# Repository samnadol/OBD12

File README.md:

# OBD12

OBD-II dongle that bridges a vehicle's CAN bus (ISO 15765-4, 500 kbit/s) to Bluetooth LE and USB-C serial.

- `pcb/`: KiCad 9 schematic and layout
- `firmware/OBD12/`: STM32G431 firmware (STM32CubeIDE or PlatformIO)
- `firmware/BLUENRG-M2SP_DTM_SPI.hex`: image for the BLE module
- `software/`: Python host library and CLI
- `docs/protocol.md`: host protocol

## Hardware

- STM32G431KBT6, 32 MHz HSE
- TCAN337 CAN transceiver on FDCAN1. No termination fitted (R16/R17/C18 are DNP for bench use).
- BlueNRG-M2SP over SPI1
- FT230X USB UART on USART1, 115200 8N1
- Powered from OBD pin 16 (12 V vehicles only) or USB-C. LM2842 buck and SPX3819 LDO, OR'd with LM66100 ideal diodes, USB has priority.
- SWD on Tag-Connect TC2030-NL: J1 for the STM32, J5 for the BlueNRG. The board must be powered while programming.

LEDs: PWR (3.3 V), S1 (on idle, blinks with a BLE connection), S2 (CAN bus healthy and ECUs responding), RX/TX (USB).

## Setup

1. Flash `BLUENRG-M2SP_DTM_SPI.hex` to the BLE module through J5.
2. Flash the STM32 firmware through J1.
3. Program the FT230X EEPROM with FT_PROG so its serial number starts with `OBD12_`. The host library finds the board by this serial.

## Firmware

- **CubeIDE:** import `firmware/OBD12` as an existing project.
- **PlatformIO:** from `firmware/OBD12`, run `pio run`, or `pio run -t upload` to flash with an ST-Link. Keep its include paths in sync with `.cproject`.

The firmware is a main loop: interrupts only fill ring buffers or set flags, and a 3 s watchdog resets the MCU if the loop stalls. USB and BLE (Nordic UART service) carry the same framed protocol.

BLE pairing uses a passkey derived from the MCU UID; `info` over USB shows it. Over BLE, reset, clear bonds and non-read-only OBD requests (e.g. clearing DTCs) need a paired link.

## Software

```
cd software
pip install -r requirements.txt
python -m obd12 info          # USB, auto-detected
python -m obd12 --ble live    # BLE
```

Commands: `info`, `power`, `can-stats`, `vin`, `pids`, `obd`, `live`, `log`, `ping`, `reset`, `clear-bonds`.

The firmware reads the VIN and the vehicle's supported mode 01 PIDs at startup. `pids` lists them, and `live --pids supported` polls all of them (up to 32). The web app reads both when it connects and offers every supported PID in its live data section.

`software/web/` is a browser app using Web Bluetooth (Bluefy on iOS, Chrome or Edge elsewhere) or Web Serial for USB (desktop Chrome or Edge). It shows the vehicle's make and model (decoded from the VIN with [corgi](https://github.com/cardog-ai/corgi), which downloads a 25 MB copy of the NHTSA vPIC database the first time it sees a new VIN), live gauges with CSV recording, and trouble codes. Diagnostics such as power, CAN statistics and the device log stay in the CLI. It keeps one connection open and reconnects on its own. It has no build step, but it must be served over HTTPS or from `localhost`:

```
cd software/web
python3 -m http.server     # http://localhost:8000
```

Pushes to `master` that touch `software/web/` publish it to GitHub Pages (`.github/workflows/pages.yml`) at https://samnadol.github.io/OBD12/.

## Known issues

- No output capacitor directly on the USB LDO output (`USB_REG_OUT`).
- The power priority logic depends on LM66100 `ST` polarity. Check that 3.3 V stays up with USB and 12 V both connected.
- The ADC reads the regulator outputs without a divider, so the readings sit near full scale. They only work as presence detection.
- Check that C23 on the 12 V rail is rated for at least 25 V.
- R10/R11 (60 Ω) drive the FT230X LEDs harder than the CBUS default.
- When running on 12 V only, PA9 back-powers the unpowered FT230X.
- U9 pad 21 (GND) is unconnected in the netlist.
- No reverse-polarity protection on the 12 V input.

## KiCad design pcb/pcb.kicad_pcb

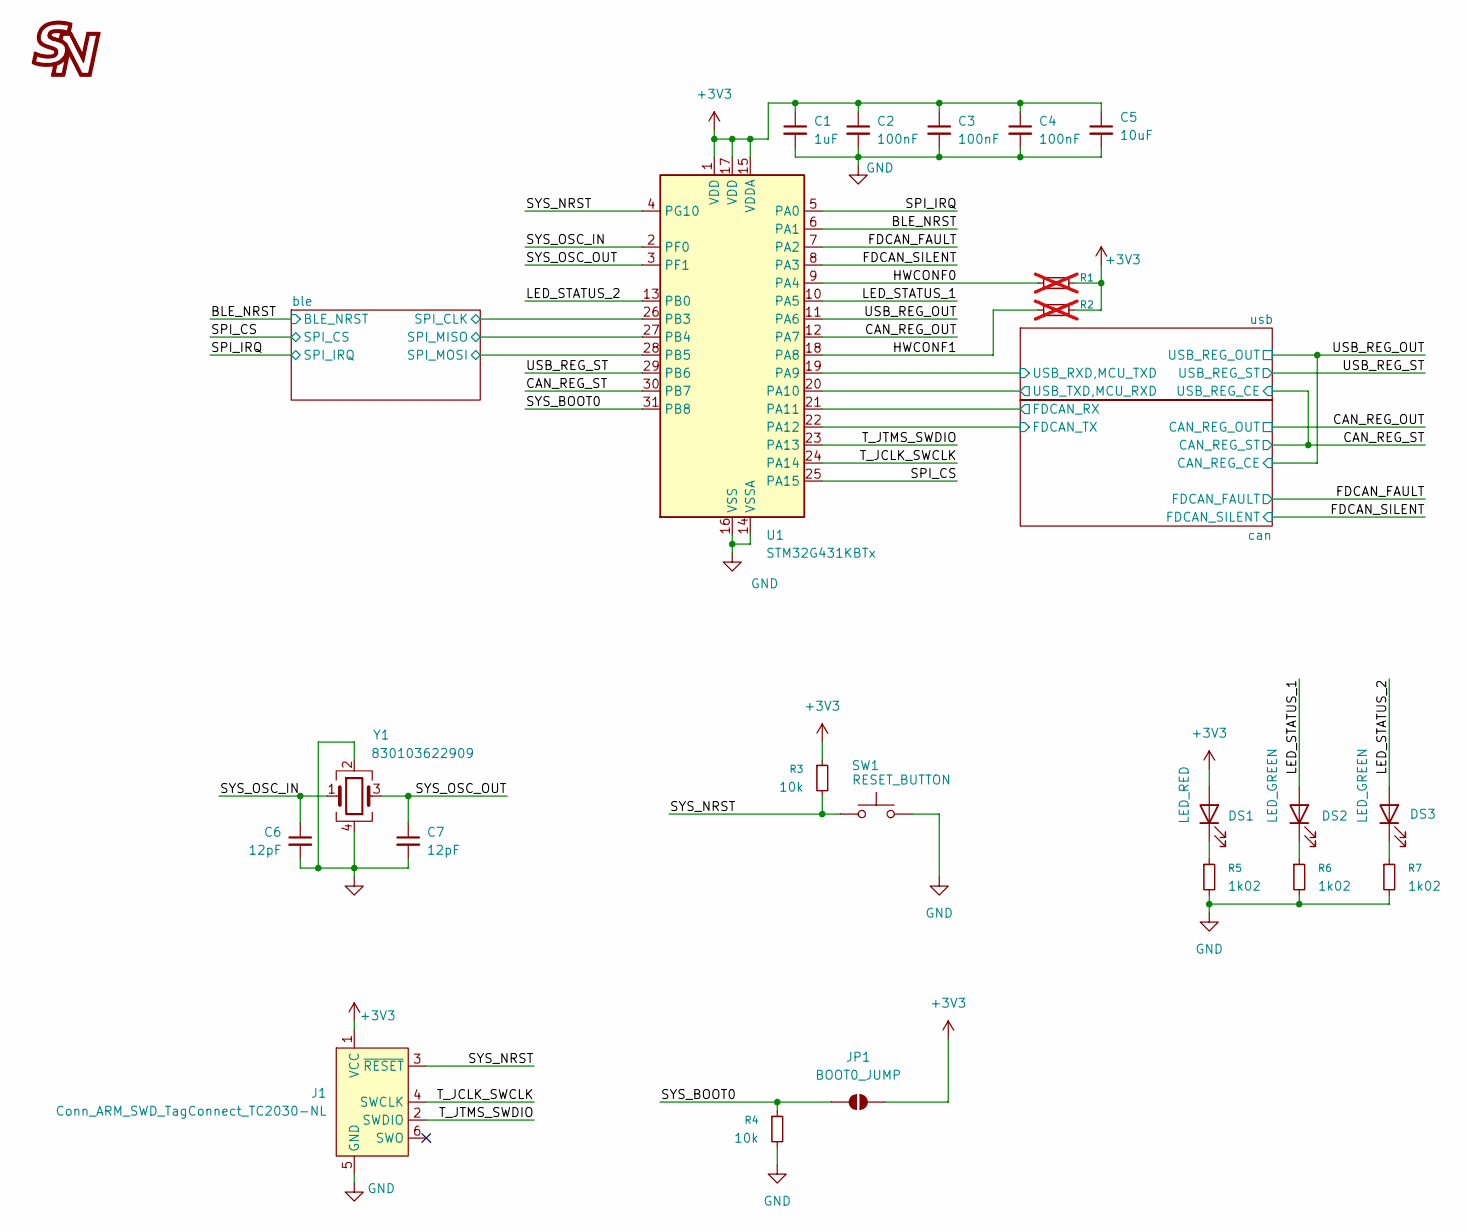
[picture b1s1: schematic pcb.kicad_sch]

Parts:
C1: 1uF; C_0603_1608Metric; LCSC C559769
C2, C3, C4: 100nF; C_0603_1608Metric; LCSC C14663
C5: 10uF; C_0603_1608Metric; LCSC C92487
C6, C7: 12pF; C_0603_1608Metric; LCSC C107034
DS1: LED_RED; LED_0603_1608Metric; LCSC C965799
DS2, DS3: LED_GREEN; LED_0603_1608Metric; LCSC C965804
G1: LOGO; logo
J1: Conn_ARM_SWD_TagConnect_TC2030-NL; Tag-Connect_TC2030-IDC-NL_2x03_P1.27mm_Vertical
JP1: BOOT0_JUMP; SolderJumper-2_P1.3mm_Open_Pad1.0x1.5mm
R1, R2: 0R; R_0603_1608Metric; LCSC C21189; not fitted
R3, R4: 10k; R_0603_1608Metric; LCSC C25804
R5, R6, R7: 1k02; R_0603_1608Metric; LCSC C22831
SW1: RESET_BUTTON; TS-1187A-ABAB; LCSC C318884
U1: STM32G431KBTx; LQFP-32_7x7mm_P0.8mm; LCSC C5270317
Y1: 830103622909; Crystal_SMD_3225-4Pin_3.2x2.5mm; LCSC C9009

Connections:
+3V3: C1.1, C2.1, C3.1, C4.1, C5.1, DS1.2 (A), J1.1 (VCC), JP1.2 (B), R1.2, R2.2, R3.1, U1.1 (VDD), U1.15 (VDDA), U1.17 (VDD); also elsewhere on the board
/BLE_NRST: U1.6 (PA1); also elsewhere on the board
/CAN_REG_OUT: U1.12 (PA7); also elsewhere on the board
/CAN_REG_ST: U1.30 (PB7); also elsewhere on the board
/FDCAN_FAULT: U1.7 (PA2); also elsewhere on the board
/FDCAN_SILENT: U1.8 (PA3); also elsewhere on the board
/HWCONF0: R1.1, U1.9 (PA4)
/HWCONF1: R2.1, U1.18 (PA8)
/LED_STATUS_1: DS2.2 (A), U1.10 (PA5)
/LED_STATUS_2: DS3.2 (A), U1.13 (PB0)
/SPI_CS: U1.25 (PA15); also elsewhere on the board
/SPI_IRQ: U1.5 (PA0); also elsewhere on the board
/SYS_BOOT0: JP1.1 (A), R4.1, U1.31 (PB8)
/SYS_NRST: J1.3 (~RESET), R3.2, SW1.1, U1.4 (PG10)
/SYS_OSC_IN: C6.1, U1.2 (PF0), Y1.1
/SYS_OSC_OUT: C7.1, U1.3 (PF1), Y1.3
/T_JCLK_SWCLK: J1.4 (SWCLK), U1.24 (PA14)
/T_JTMS_SWDIO: J1.2 (SWDIO), U1.23 (PA13)
/USB_REG_OUT: U1.11 (PA6); also elsewhere on the board
/USB_REG_ST: U1.29 (PB6); also elsewhere on the board
/ble/SPI_CLK: U1.26 (PB3); also elsewhere on the board
/ble/SPI_MISO: U1.27 (PB4); also elsewhere on the board
/ble/SPI_MOSI: U1.28 (PB5); also elsewhere on the board
/can/FDCAN_RX: U1.21 (PA11); also elsewhere on the board
/can/FDCAN_TX: U1.22 (PA12); also elsewhere on the board
/usb/USB_RXD,MCU_TXD: U1.19 (PA9); also elsewhere on the board
/usb/USB_TXD,MCU_RXD: U1.20 (PA10); also elsewhere on the board
GND: C1.2, C2.2, C3.2, C4.2, C5.2, C6.2, C7.2, J1.5 (GND), R4.2, R5.2, R6.2, R7.2, SW1.2, U1.14 (VSSA), U1.16 (VSS), U1.32 (VSS), Y1.2, Y1.4; also elsewhere on the board
unnamed: DS1.1 (K), R5.1
unnamed: DS2.1 (K), R6.1
unnamed: DS3.1 (K), R7.1

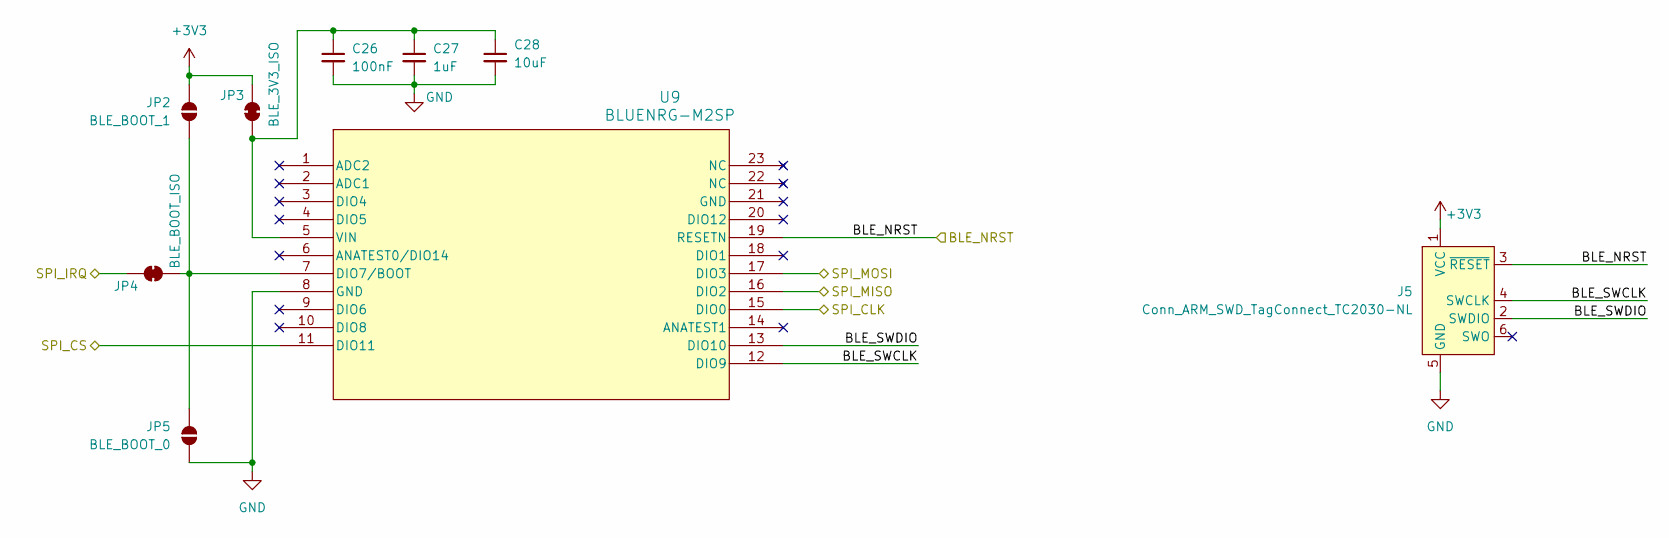
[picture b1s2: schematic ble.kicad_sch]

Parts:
C26: 100nF; C_0603_1608Metric; LCSC C14663
C27: 1uF; C_0603_1608Metric; LCSC C559769
C28: 10uF; C_0603_1608Metric; LCSC C92487
J5: Conn_ARM_SWD_TagConnect_TC2030-NL; Tag-Connect_TC2030-IDC-NL_2x03_P1.27mm_Vertical
JP2: BLE_BOOT_1; SolderJumper-2_P1.3mm_Open_Pad1.0x1.5mm
JP3: BLE_3V3_ISO; SolderJumper-2_P1.3mm_Bridged_Pad1.0x1.5mm
JP4: BLE_BOOT_ISO; SolderJumper-2_P1.3mm_Bridged_Pad1.0x1.5mm
JP5: BLE_BOOT_0; SolderJumper-2_P1.3mm_Open_Pad1.0x1.5mm
U9: BLUENRG-M2SP; BLUENRG-2M_STM; LCSC C1850403

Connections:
+3V3: J5.1 (VCC), JP2.2 (B), JP3.1 (A); also elsewhere on the board
/BLE_NRST: J5.3 (~RESET), U9.19 (RESETN); also elsewhere on the board
/SPI_CS: U9.11 (DIO11); also elsewhere on the board
/SPI_IRQ: JP4.1 (A); also elsewhere on the board
/ble/BLE_SWCLK: J5.4 (SWCLK), U9.12 (DIO9)
/ble/BLE_SWDIO: J5.2 (SWDIO), U9.13 (DIO10)
/ble/SPI_CLK: U9.15 (DIO0); also elsewhere on the board
/ble/SPI_MISO: U9.16 (DIO2); also elsewhere on the board
/ble/SPI_MOSI: U9.17 (DIO3); also elsewhere on the board
GND: C26.2, C27.2, C28.2, J5.5 (GND), JP5.1 (A), U9.8 (GND); also elsewhere on the board
unnamed: JP2.1 (A), JP4.2 (B), JP5.2 (B), U9.7 (DIO7/BOOT)
unnamed: C26.1, C27.1, C28.1, JP3.2 (B), U9.5 (VIN)

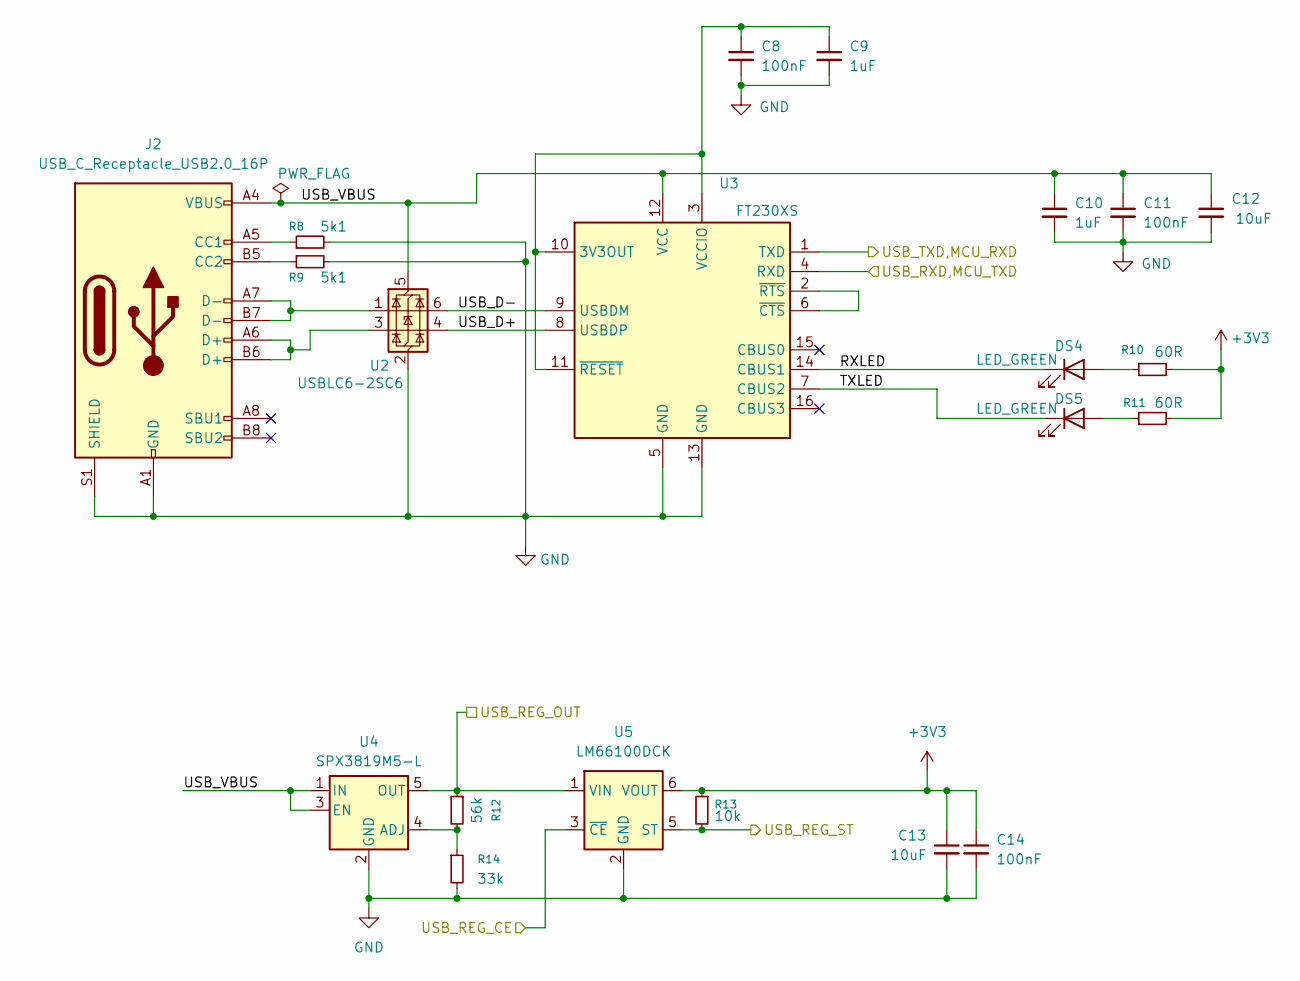
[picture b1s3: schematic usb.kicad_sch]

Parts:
C8, C11, C14: 100nF; C_0603_1608Metric; LCSC C14663
C9, C10: 1uF; C_0603_1608Metric; LCSC C559769
C12, C13: 10uF; C_0603_1608Metric; LCSC C92487
DS4, DS5: LED_GREEN; LED_0603_1608Metric; LCSC C965804
J2: USB_C_Receptacle_USB2.0_16P; USB_C_Receptacle_G-Switch_GT-USB-7010ASV; LCSC C2988369
R8, R9: 5k1; R_0603_1608Metric; LCSC C23186
R10, R11: 60R; R_0603_1608Metric; LCSC C166918
R12: 56k; R_0603_1608Metric; LCSC C23206
R13: 10k; R_0603_1608Metric; LCSC C25804
R14: 33k; R_0603_1608Metric; LCSC C4216
U2: USBLC6-2SC6; SOT-23-6; LCSC C7519
U3: FT230XS; SSOP-16_3.9x4.9mm_P0.635mm; LCSC C69082
U4: SPX3819M5-L; SOT-23-5; LCSC C9056
U5: LM66100DCK; SOT-363_SC-70-6; LCSC C2869734

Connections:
+3V3: C13.1, C14.1, R10.2, R11.2, R13.1, U5.6 (VOUT); also elsewhere on the board
/CAN_REG_ST: U5.3 (~CE); also elsewhere on the board
/USB_REG_OUT: R12.1, U4.5 (OUT), U5.1 (VIN); also elsewhere on the board
/USB_REG_ST: R13.2, U5.5 (ST); also elsewhere on the board
/usb/RXLED: DS4.1 (K), U3.14 (CBUS1)
/usb/TXLED: DS5.1 (K), U3.7 (CBUS2)
/usb/USB_D+: U2.4 (I/O2), U3.8 (USBDP)
/usb/USB_D-: U2.6 (I/O1), U3.9 (USBDM)
/usb/USB_RXD,MCU_TXD: U3.4 (RXD); also elsewhere on the board
/usb/USB_TXD,MCU_RXD: U3.1 (TXD); also elsewhere on the board
/usb/USB_VBUS: C10.1, C11.1, C12.1, J2.A4 (VBUS), J2.A9 (VBUS), J2.B4 (VBUS), J2.B9 (VBUS), U2.5 (VBUS), U3.12 (VCC), U4.1 (IN), U4.3 (EN)
GND: C8.2, C9.2, C10.2, C11.2, C12.2, C13.2, C14.2, J2.A1 (GND), J2.A12 (GND), J2.B1 (GND), J2.B12 (GND), J2.S1 (SHIELD), R8.2, R9.2, R14.2, U2.2 (GND), U3.5 (GND), U3.13 (GND), U4.2 (GND), U5.2 (GND); also elsewhere on the board
unnamed: DS4.2 (A), R10.1
unnamed: DS5.2 (A), R11.1
unnamed: J2.A5 (CC1), R8.1
unnamed: J2.B5 (CC2), R9.1
unnamed: J2.A6 (D+), J2.B6 (D+), U2.3 (I/O2)
unnamed: J2.A7 (D-), J2.B7 (D-), U2.1 (I/O1)
unnamed: C8.1, C9.1, U3.3 (VCCIO), U3.10 (3V3OUT), U3.11 (~RESET)
unnamed: U3.2 (~RTS), U3.6 (~CTS)
unnamed: R12.2, R14.1, U4.4 (ADJ)

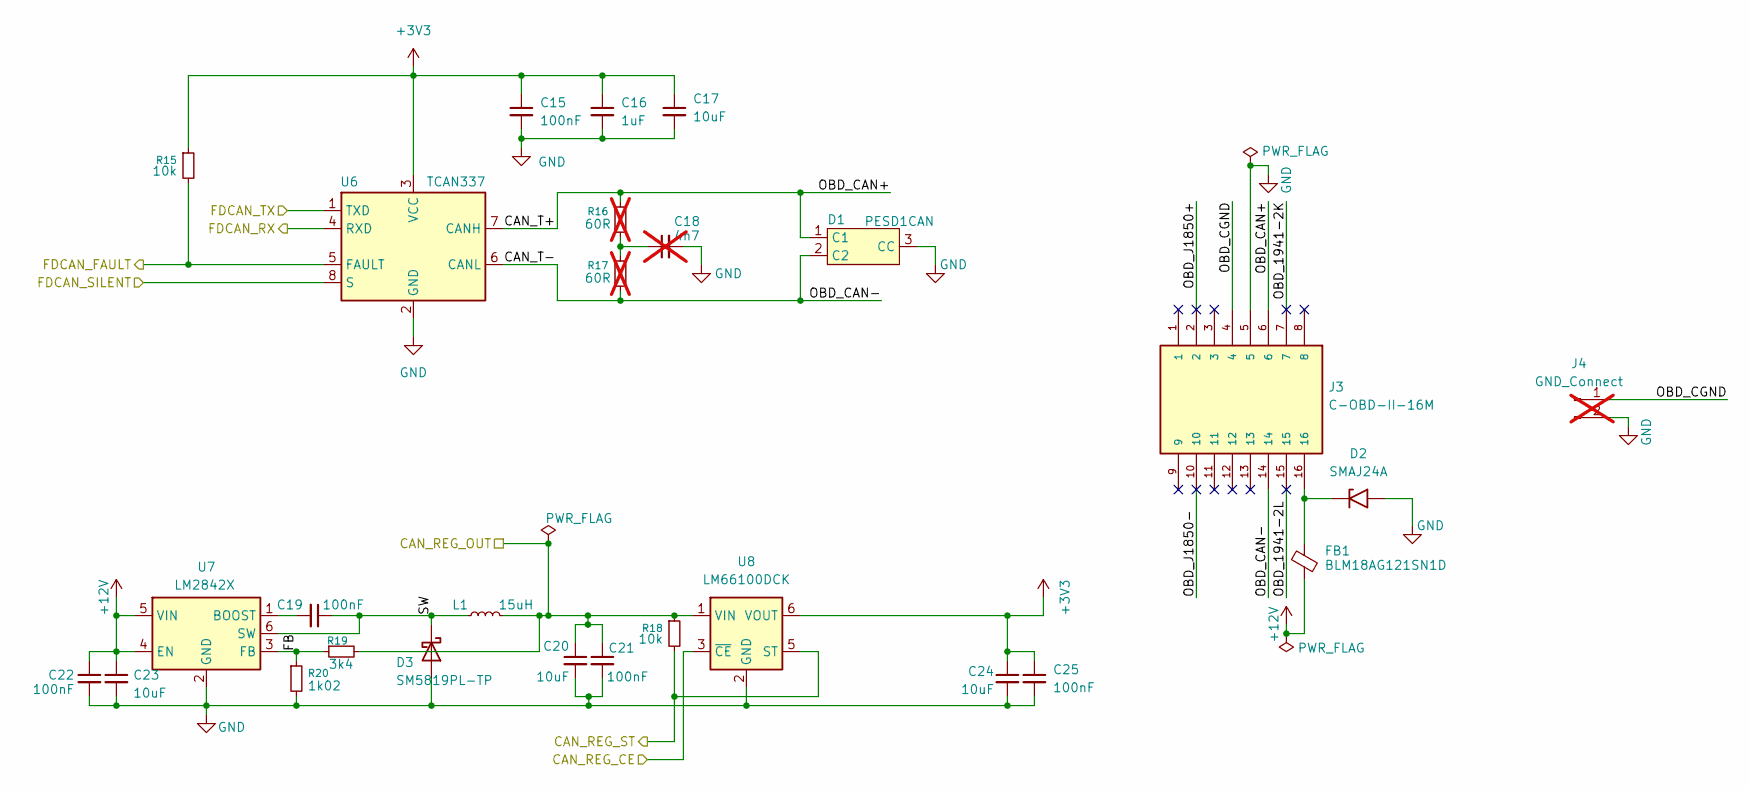
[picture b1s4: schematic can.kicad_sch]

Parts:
C15, C19, C21, C22, C25: 100nF; C_0603_1608Metric; LCSC C14663
C16: 1uF; C_0603_1608Metric; LCSC C559769
C17, C20, C23, C24: 10uF; C_0603_1608Metric; LCSC C92487
C18: 4n7; C_0603_1608Metric; LCSC C106218; not fitted
D1: PESD1CAN; TSOT-23; LCSC C15771
D2: SMAJ24A; D_SMA; LCSC C113962
D3: SM5819PL-TP; D_SOD-123F; LCSC C669023
FB1: BLM18AG121SN1D; L_0603_1608Metric; LCSC C76892
J3: C-OBD-II-16M; COMTECH_C-OBD-II-16M
J4: GND_Connect; PinHeader_1x02_P2.54mm_Vertical; not fitted
L1: 15uH; L_Wurth_WE-LQSH-3012; LCSC C668450
R15, R18: 10k; R_0603_1608Metric; LCSC C25804
R16, R17: 60R; R_0603_1608Metric; LCSC C166918; not fitted
R19: 3k4; R_0603_1608Metric; LCSC C22997
R20: 1k02; R_0603_1608Metric; LCSC C22831
U6: TCAN337; SOIC-8_3.9x4.9mm_P1.27mm; LCSC C2860648
U7: LM2842X; TSOT-23-6; LCSC C2865947
U8: LM66100DCK; SOT-363_SC-70-6; LCSC C2869734

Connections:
+3V3: C15.1, C16.1, C17.1, C24.1, C25.1, R15.1, U6.3 (VCC), U8.6 (VOUT); also elsewhere on the board
+12V: C22.1, C23.1, FB1.2, U7.4 (EN), U7.5 (VIN)
/CAN_REG_OUT: C20.1, C21.1, L1.2, R18.1, R19.2, U8.1 (VIN); also elsewhere on the board
/CAN_REG_ST: R18.2, U8.5 (ST); also elsewhere on the board
/FDCAN_FAULT: R15.2, U6.5 (FAULT); also elsewhere on the board
/FDCAN_SILENT: U6.8 (S); also elsewhere on the board
/USB_REG_OUT: U8.3 (~CE); also elsewhere on the board
/can/CAN_T+: D1.1 (C1), J3.6, R16.1, U6.7 (CANH)
/can/CAN_T-: D1.2 (C2), J3.14, R17.1, U6.6 (CANL)
/can/FB: R19.1, R20.1, U7.3 (FB)
/can/FDCAN_RX: U6.4 (RXD); also elsewhere on the board
/can/FDCAN_TX: U6.1 (TXD); also elsewhere on the board
/can/OBD_1941-2K: J3.7
/can/OBD_1941-2L: J3.15
/can/OBD_CGND: J3.4, J4.1
/can/OBD_J1850+: J3.2
/can/OBD_J1850-: J3.10
/can/SW: C19.1, D3.1 (K), L1.1, U7.6 (SW)
GND: C15.2, C16.2, C17.2, C18.2, C20.2, C21.2, C22.2, C23.2, C24.2, C25.2, D1.3 (CC), D2.2 (A2), D3.2 (A), J3.5, J4.2, R20.2, U6.2 (GND), U7.2 (GND), U8.2 (GND); also elsewhere on the board
unnamed: C18.1, R16.2, R17.2
unnamed: D2.1 (A1), FB1.1, J3.16
unnamed: C19.2, U7.1 (BOOST)

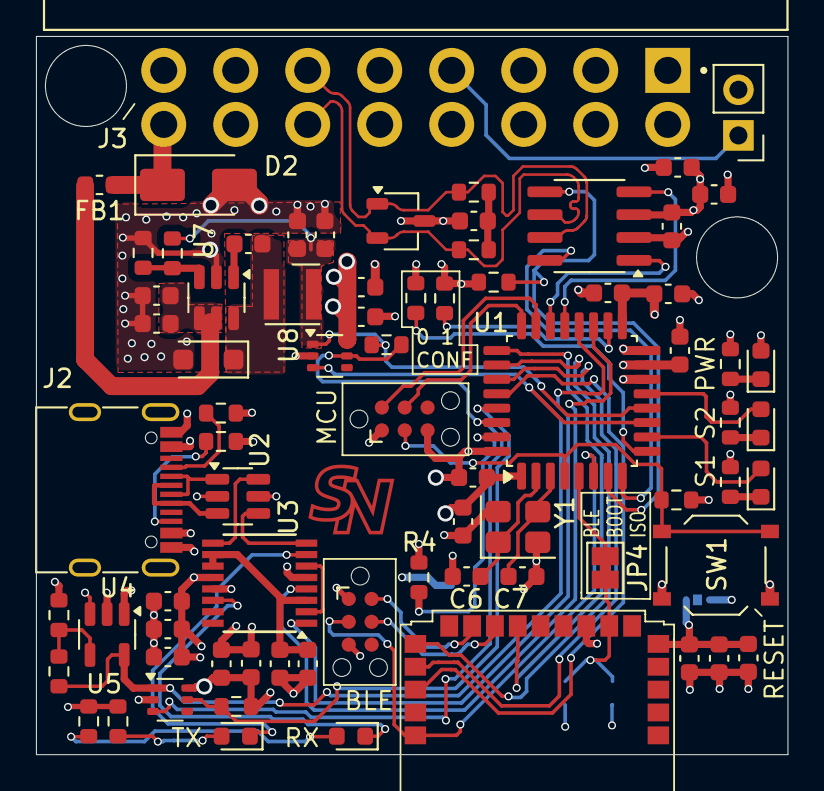
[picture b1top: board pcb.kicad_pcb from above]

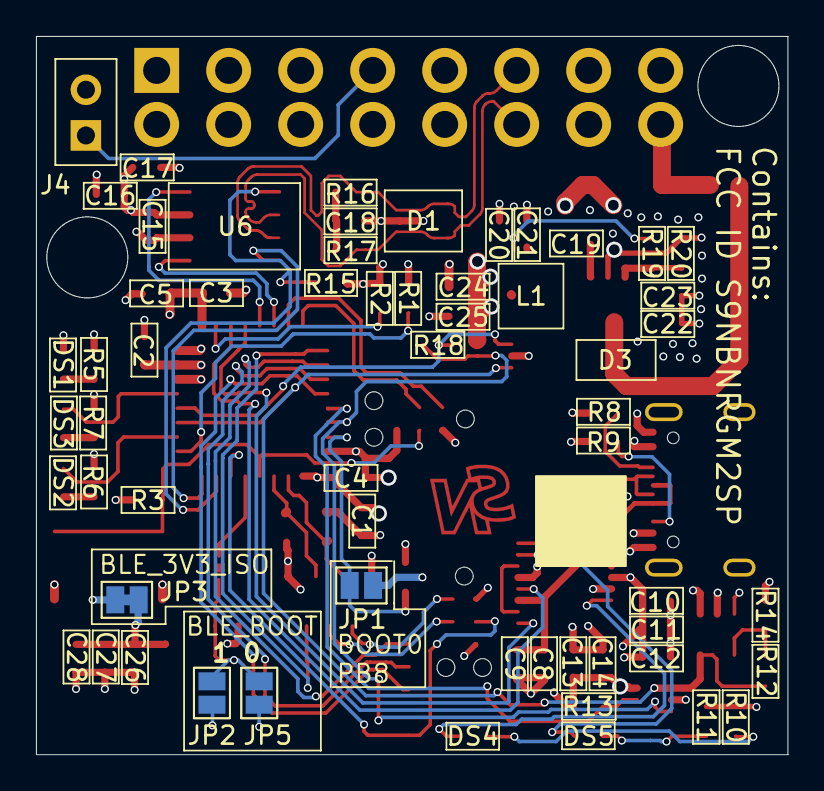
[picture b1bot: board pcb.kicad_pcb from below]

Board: 4 copper layers, 41.8 x 39.9 mm, 80 parts (4 on the bottom side), 58 nets.

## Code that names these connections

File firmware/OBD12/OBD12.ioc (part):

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Mcu.Name=STM32G431K(6-8-B)Tx
Mcu.Package=LQFP32
Mcu.UserName=STM32G431KBTx
PA0.GPIOParameters=GPIO_Label
PA0.GPIO_Label=SPI1_IRQ
PA0.Signal=GPXTI0
PA1.GPIOParameters=GPIO_Label
PA1.GPIO_Label=BLE_NRST
PA1.Signal=GPIO_Output
PA10.GPIOParameters=GPIO_Speed
PA10.GPIO_Speed=GPIO_SPEED_FREQ_MEDIUM
PA10.Mode=Asynchronous
PA10.Signal=USART1_RX
PA11.GPIOParameters=GPIO_Speed
PA11.GPIO_Speed=GPIO_SPEED_FREQ_HIGH
PA11.Mode=FDCAN_Activate
PA11.Signal=FDCAN1_RX
PA12.GPIOParameters=GPIO_Speed
PA12.GPIO_Speed=GPIO_SPEED_FREQ_HIGH
PA12.Mode=FDCAN_Activate
PA12.Signal=FDCAN1_TX
PA13.Mode=Serial_Wire
PA13.Signal=SYS_JTMS-SWDIO
PA14.Mode=Serial_Wire
PA14.Signal=SYS_JTCK-SWCLK
PA15.GPIOParameters=GPIO_Label
PA15.GPIO_Label=SPI1_CS
PA15.Signal=GPIO_Output
PA2.GPIOParameters=GPIO_Label
PA2.GPIO_Label=FDCAN_FAULT
PA2.Signal=GPXTI2
PA3.GPIOParameters=GPIO_Label
PA3.GPIO_Label=FDCAN_SILENT
PA3.Signal=GPIO_Output
PA4.GPIOParameters=GPIO_PuPd,GPIO_Label
PA4.GPIO_Label=HWCONF0
PA4.GPIO_PuPd=GPIO_PULLDOWN
PA4.Signal=GPIO_Input
PA5.GPIOParameters=GPIO_Label
PA5.GPIO_Label=STATUS_LED_1
PA5.Signal=GPIO_Output
PA6.GPIOParameters=GPIO_Label,GPIO_Pd
PA6.GPIO_Label=USB_REG_OUT
PA6.GPIO_Pd=GPIO_PULLDOWN
PA6.Mode=IN3-Single-Ended
PA6.Signal=ADC2_IN3
PA7.GPIOParameters=GPIO_Label,GPIO_Pd
PA7.GPIO_Label=CAN_REG_OUT
PA7.GPIO_Pd=GPIO_PULLDOWN
PA7.Mode=IN4-Single-Ended
PA7.Signal=ADC2_IN4
PA8.GPIOParameters=GPIO_PuPd,GPIO_Label
PA8.GPIO_Label=HWCONF1
PA8.GPIO_PuPd=GPIO_PULLDOWN
PA8.Signal=GPIO_Input
PA9.GPIOParameters=GPIO_Speed
PA9.GPIO_Speed=GPIO_SPEED_FREQ_MEDIUM
PA9.Mode=Asynchronous
PA9.Signal=USART1_TX
PB0.GPIOParameters=GPIO_Label
PB0.GPIO_Label=STATUS_LED_2
PB0.Signal=GPIO_Output
PB3.GPIOParameters=GPIO_Speed
PB3.GPIO_Speed=GPIO_SPEED_FREQ_MEDIUM
PB3.Mode=Full_Duplex_Master
PB3.Signal=SPI1_SCK
PB4.GPIOParameters=GPIO_Speed
PB4.GPIO_Speed=GPIO_SPEED_FREQ_MEDIUM
PB4.Mode=Full_Duplex_Master
PB4.Signal=SPI1_MISO
PB5.GPIOParameters=GPIO_Speed
PB5.GPIO_Speed=GPIO_SPEED_FREQ_MEDIUM
PB5.Mode=Full_Duplex_Master
PB5.Signal=SPI1_MOSI
PB6.GPIOParameters=GPIO_Label
PB6.GPIO_Label=USB_REG_ST
PB6.Signal=GPIO_Input
PB7.GPIOParameters=GPIO_Label
PB7.GPIO_Label=CAN_REG_ST
PB7.Signal=GPIO_Input
PF0-OSC_IN.Mode=HSE-External-Oscillator
PF0-OSC_IN.Signal=RCC_OSC_IN
PF1-OSC_OUT.Mode=HSE-External-Oscillator
PF1-OSC_OUT.Signal=RCC_OSC_OUT
RCC.HSE_VALUE=32000000
RCC.SYSCLKFreq_VALUE=32000000
RCC.SYSCLKSource=RCC_SYSCLKSOURCE_HSE
board=custom

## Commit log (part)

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2025-08-08 add initial files
2025-08-08 organize
2025-08-11 add can etc
2025-08-15 add slot for filter
2025-09-14 lots of updates
